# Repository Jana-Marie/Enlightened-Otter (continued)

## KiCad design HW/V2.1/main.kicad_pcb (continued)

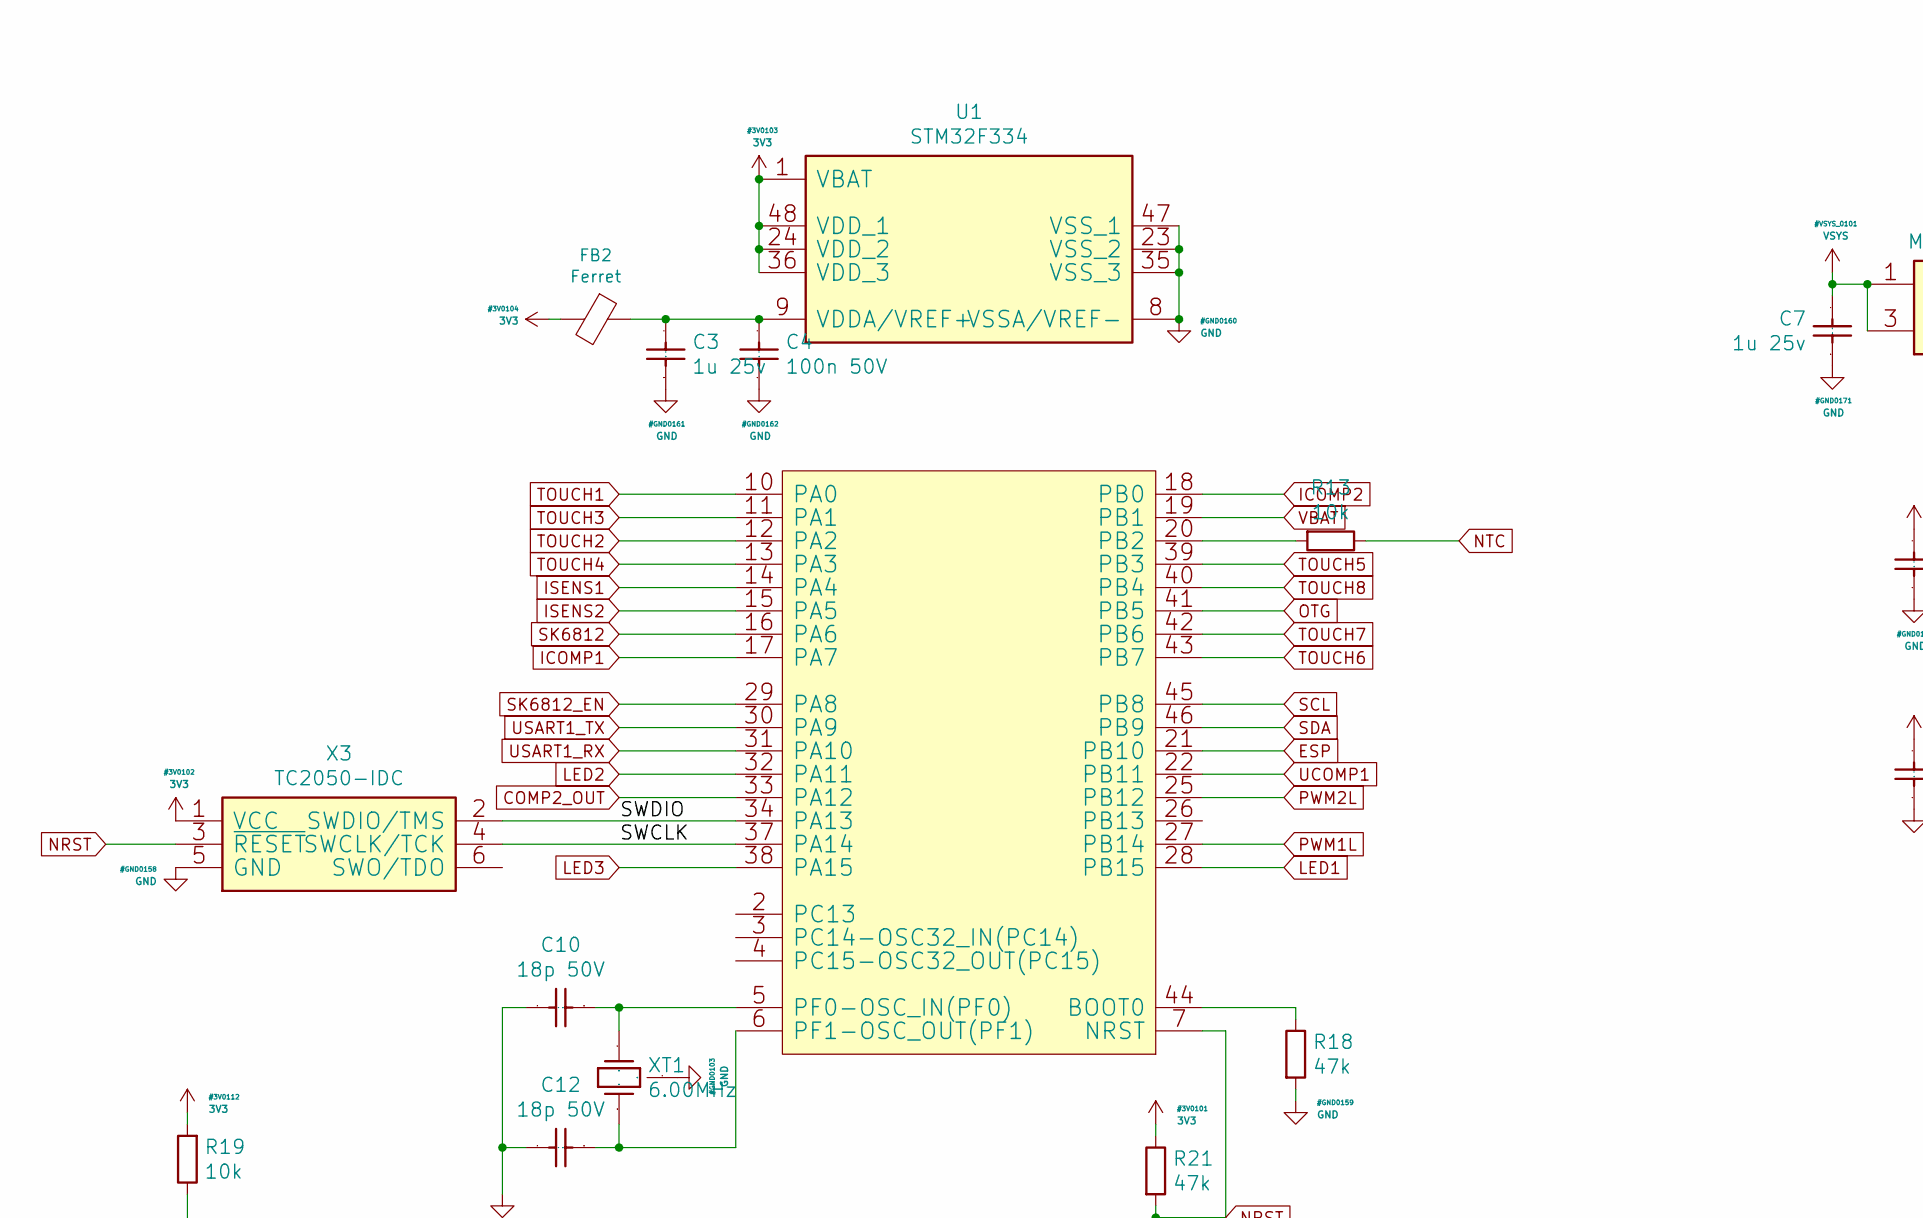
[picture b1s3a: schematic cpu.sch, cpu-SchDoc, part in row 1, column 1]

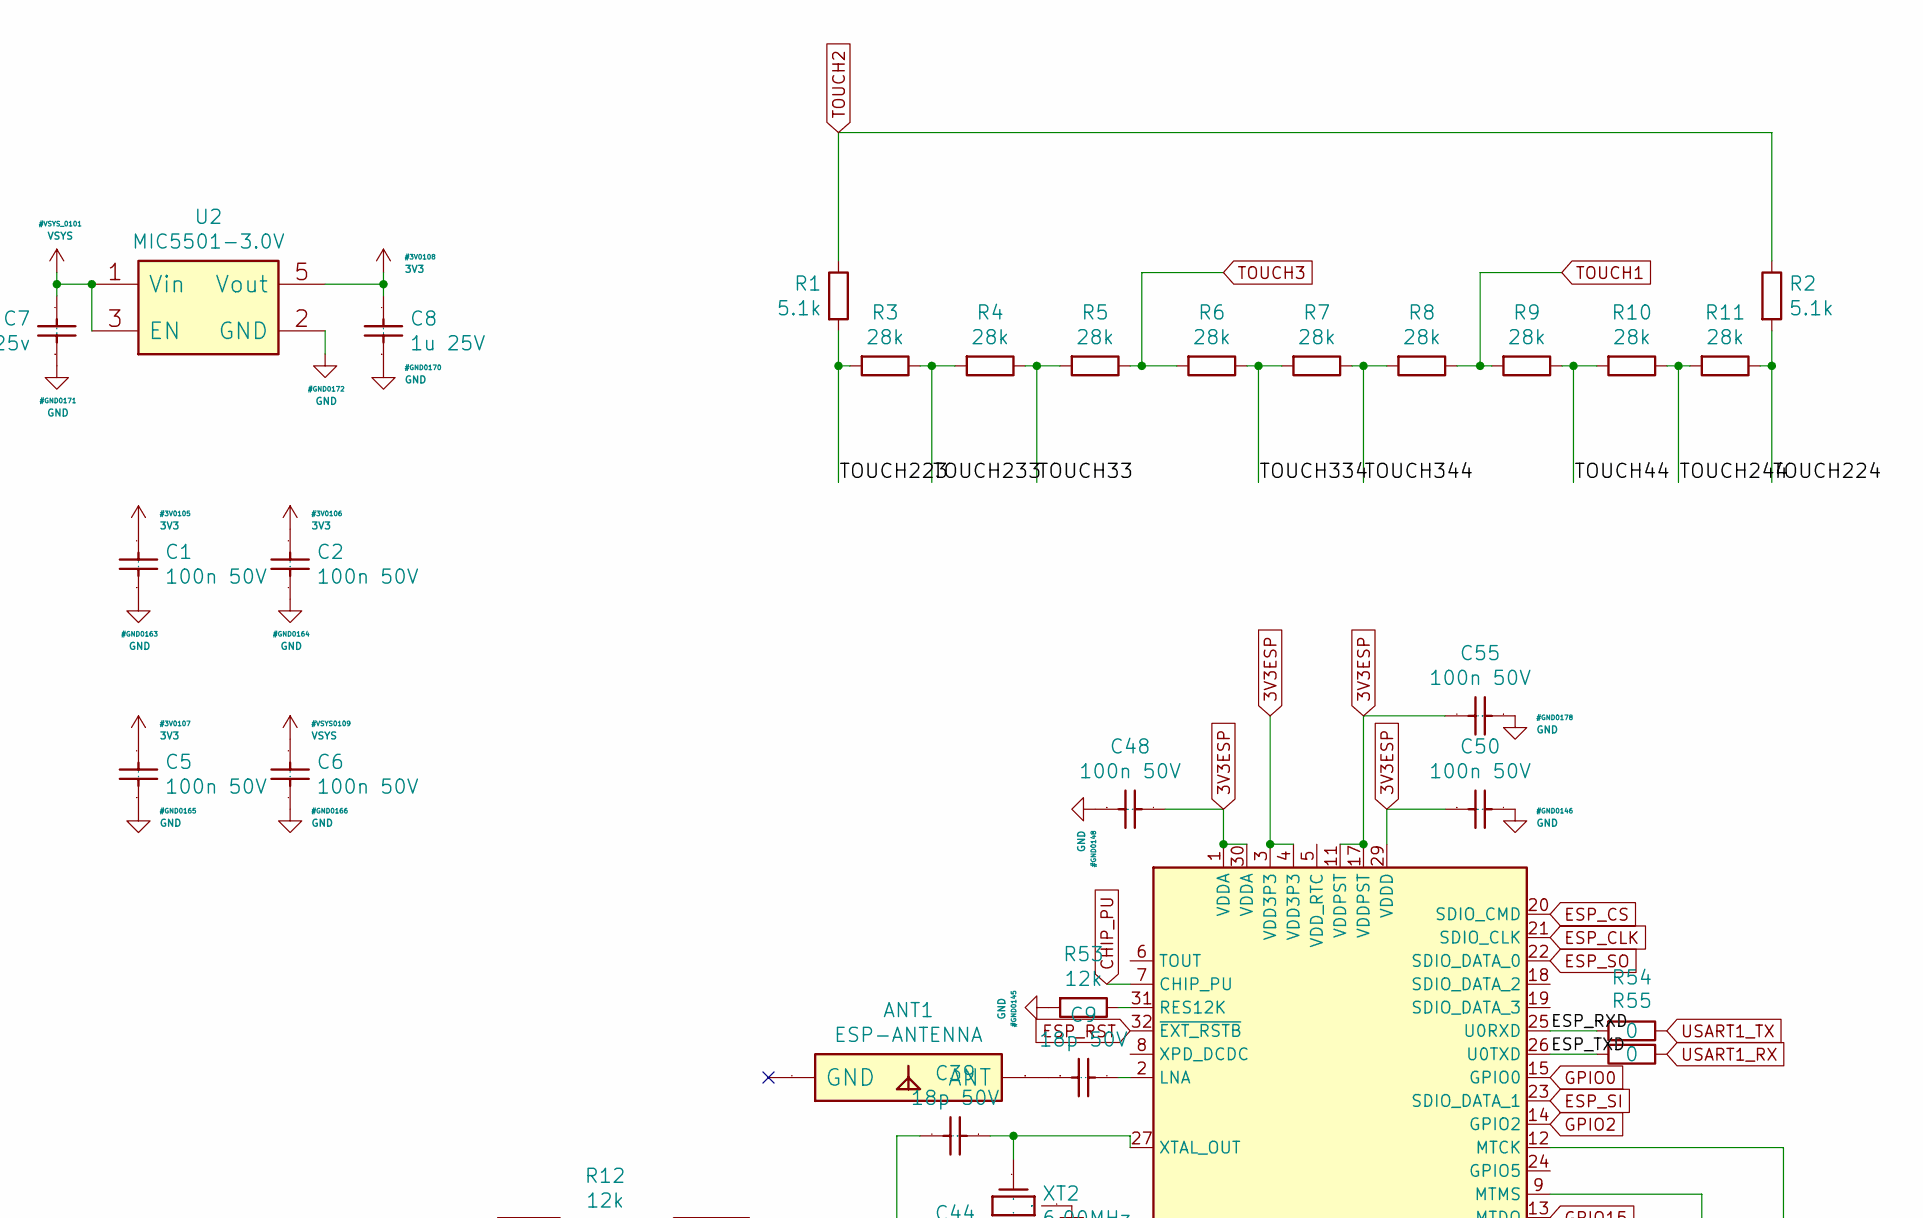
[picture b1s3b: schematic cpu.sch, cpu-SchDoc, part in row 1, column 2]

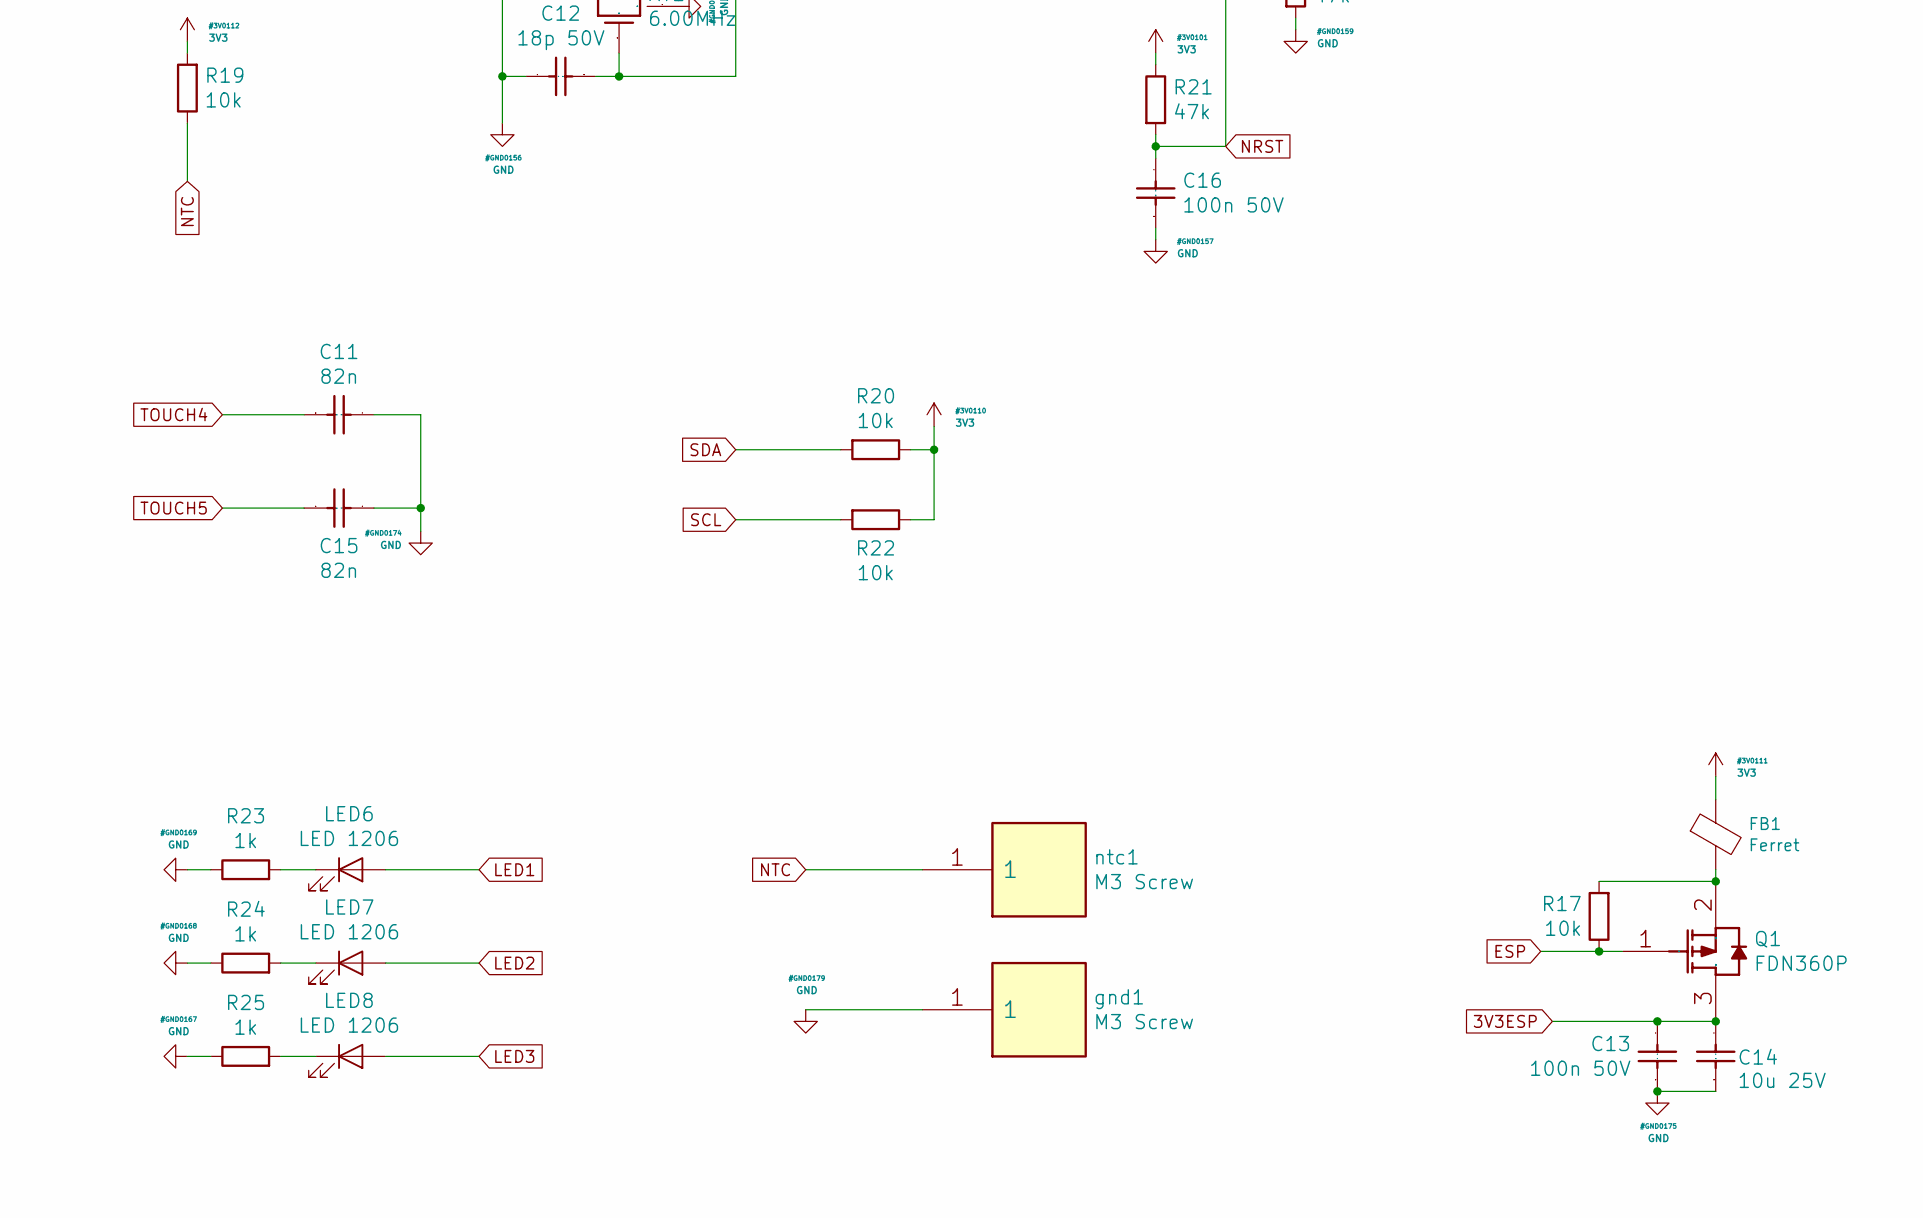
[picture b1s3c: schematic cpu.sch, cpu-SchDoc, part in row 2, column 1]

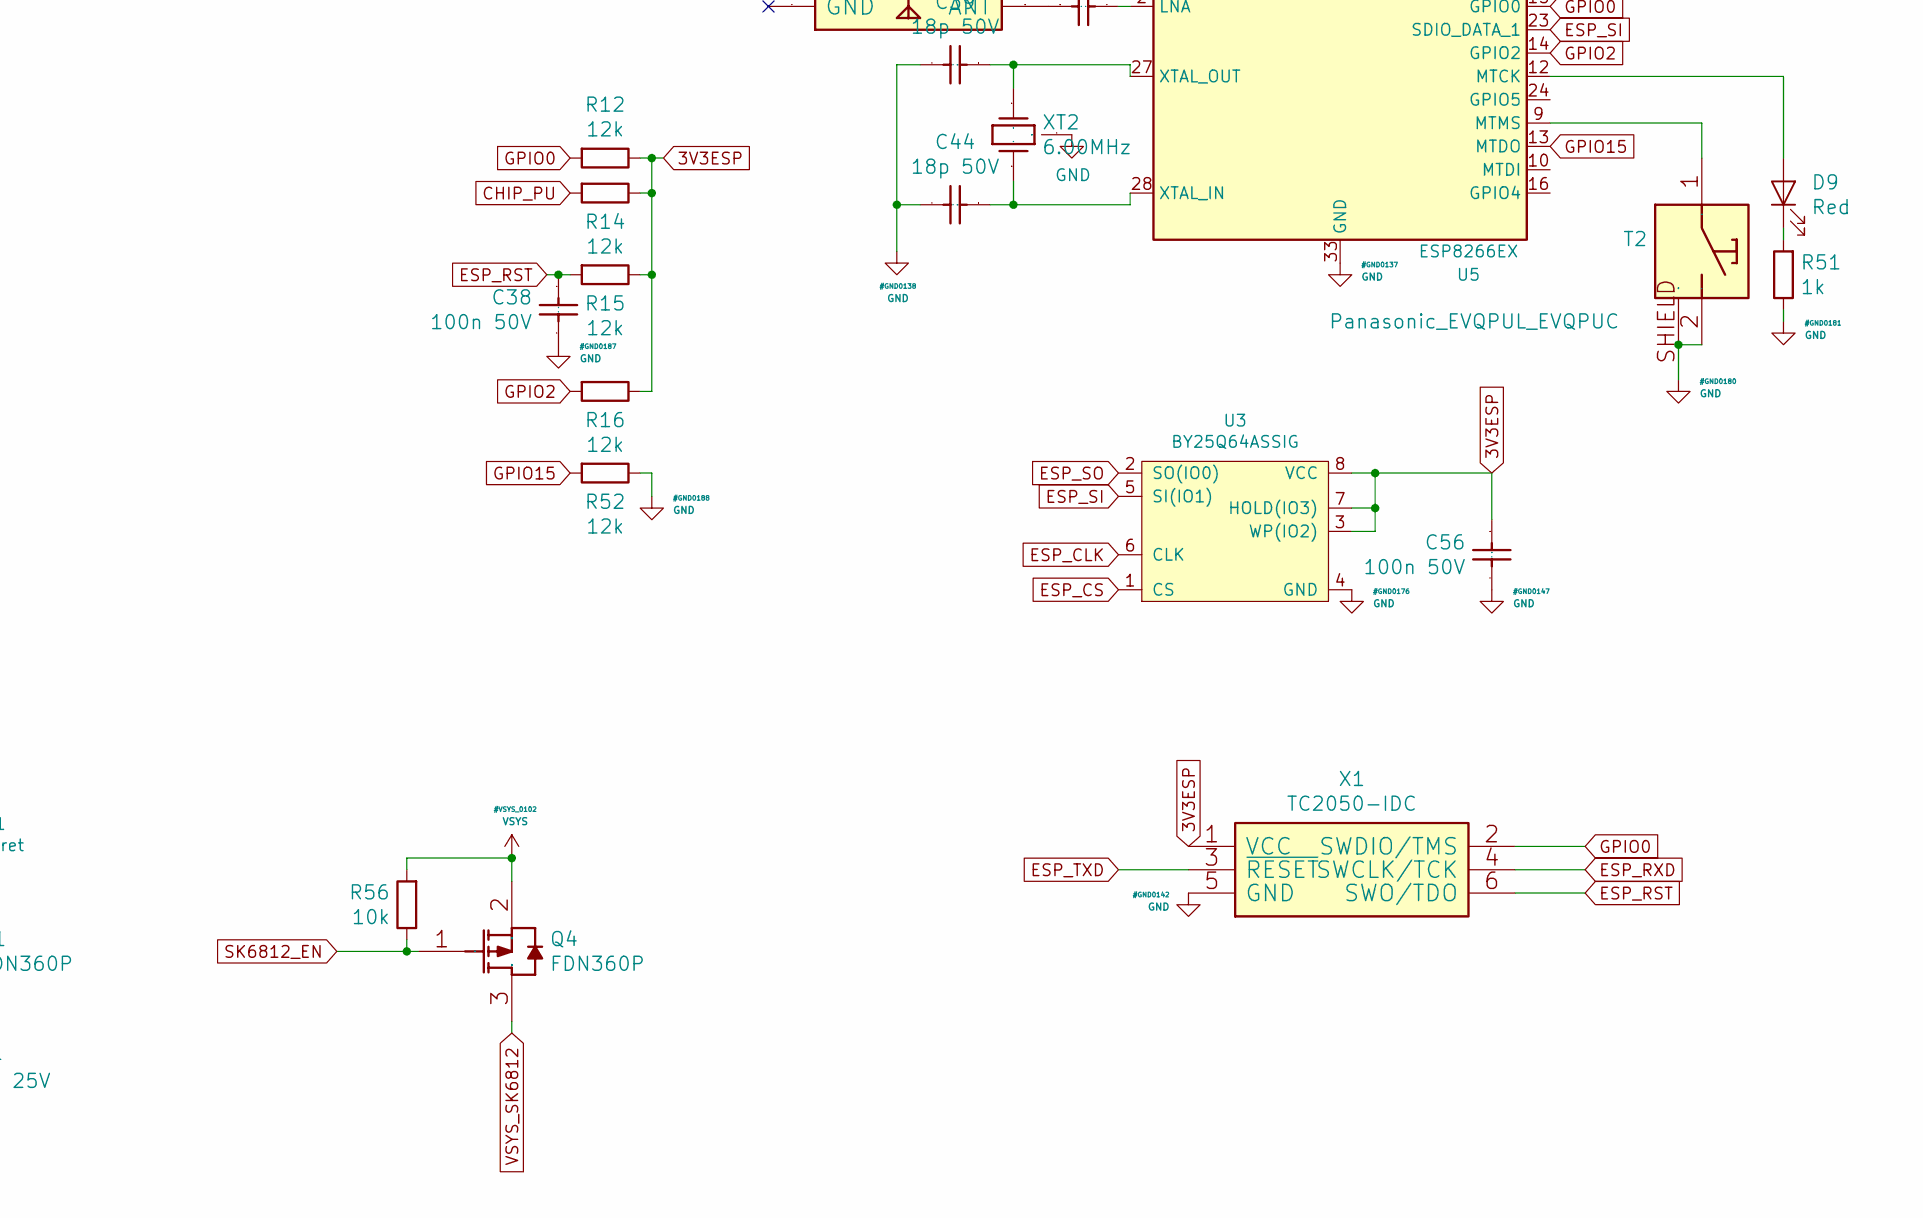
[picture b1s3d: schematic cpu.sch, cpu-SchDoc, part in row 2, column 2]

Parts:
ANT1: ESP-ANTENNA; AN9520_Rainsun
C1, C2, C4, C5, C6, C13, C16, C38, C48, C50, C55, C56: 100n 50V; C_0603_1608Metric
C3, C7: 1u 25v; C_0603_1608Metric
C8: 1u 25V; C_0603_1608Metric
C9, C10, C12, C39, C44: 18p 50V; C_0603_1608Metric
C11, C15: 82n; C_0603_1608Metric
C14: 10u 25V; C_0805_2012Metric
D9: Red; LED_0603_1608Metric
FB1, FB2: Ferret; L_0805_2012Metric
LED6, LED7, LED8: LED 1206; LED_1206_3216_BACK
Q1, Q4: FDN360P; SOT-23
R1, R2: 5.1k; R_0603_1608Metric
R3, R4, R5, R6, R7, R8, R9, R10, R11: 28k; R_0603_1608Metric
R12, R14, R15, R16, R52, R53: 12k; R_0603_1608Metric
R13, R17, R19, R20, R22, R56: 10k; R_0603_1608Metric
R18, R21: 47k; R_0603_1608Metric
R23, R24, R25, R51: 1k; R_0603_1608Metric
R54, R55: 0; R_0603_1608Metric
T2: Panasonic_EVQPUL_EVQPUC
U1: STM32F334; TQFP-48_7x7mm_P0.5mm
U2: MIC5501-3.0V; SOT-23-5
U3: BY25Q64ASSIG; SSOP-8_5.25x5.24mm_P1.27mm_WIDE_MULTI
U5: ESP8266EX; QFN-32-1EP_5x5mm_P0.5mm_EP3.45x3.45mm
X1, X3: TC2050-IDC; TC2030
XT1, XT2: 6.00MHz; Oscillator_3225
gnd1: M3 Screw; M3_Screw
ntc1: M3 Screw; M3_Screw

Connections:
3V3: C1.2, C2.2, C5.2, C8.2, FB1.1, FB2.2, R19.2, R20.1, R21.1, R22.1, U1.1 (VBAT), U1.24 (VDD_2), U1.36 (VDD_3), U1.48 (VDD_1), U2.5 (Vout), X3.1 (VCC); also elsewhere on the board
3V3ESP: C13.2, C14.2, C48.2, C50.1, C55.2, C56.1, Q1.3 (DRAIN), R12.1, R14.1, R15.1, R16.1, U3.3 (WP(IO2)), U3.7 (HOLD(IO3)), U3.8 (VCC), U5.1 (VDDA), U5.3 (VDD3P3), U5.4 (VDD3P3), U5.11 (VDDPST), U5.17 (VDDPST), U5.29 (VDDD), U5.30 (VDDA), X1.1 (VCC)
/cpu/SWCLK: U1.37 (PA14), X3.4 (SWCLK/TCK)
/cpu/SWDIO: U1.34 (PA13), X3.2 (SWDIO/TMS)
/cpu/TOUCH33: R4.1, R5.2
/cpu/TOUCH44: R9.1, R10.2
/cpu/TOUCH223: R1.2, R3.2
/cpu/TOUCH224: R2.2, R11.1
/cpu/TOUCH233: R3.1, R4.2
/cpu/TOUCH244: R10.1, R11.2
/cpu/TOUCH334: R6.1, R7.2
/cpu/TOUCH344: R7.1, R8.2
CHIP_PU: R14.2, U5.7 (CHIP_PU)
COMP2_OUT: U1.33 (PA12)
ESP: Q1.1 (GATE), R17.1, U1.21 (PB10)
ESP_CLK: U3.6 (CLK), U5.21 (SDIO_CLK)
ESP_CS: U3.1 (CS), U5.20 (SDIO_CMD)
ESP_RST: C38.1, R15.2, U5.32 (~EXT_RSTB~), X1.6 (SWO/TDO)
ESP_RXD: R54.2, U5.25 (U0RXD), X1.4 (SWCLK/TCK)
ESP_SI: U3.5 (SI(IO1)), U5.23 (SDIO_DATA_1)
ESP_SO: U3.2 (SO(IO0)), U5.22 (SDIO_DATA_0)
ESP_TXD: R55.2, U5.26 (U0TXD), X1.3 (~RESET)
GND: C1.1, C2.1, C3.1, C4.1, C5.1, C6.1, C7.1, C8.1, C10.2, C11.2, C12.2, C13.1, C14.1, C15.2, C16.1, C38.2, C39.2, C44.2, C48.1, C50.2, C55.1, C56.2, R18.2, R23.1, R24.1, R25.1, R51.1, R52.1, R53.2, T2.2, T2.SHIELD, U1.8 (VSSA/VREF-), U1.23 (VSS_2), U1.35 (VSS_3), U1.47 (VSS_1), U2.2 (GND), U3.4 (GND), U5.33 (GND), X1.5 (GND), X3.5 (GND), XT1.2 (OUT), XT1.4 (OUT), XT2.2 (OUT), XT2.4 (OUT), gnd1.1; also elsewhere on the board
GPIO0: R12.2, U5.15 (GPIO0), X1.2 (SWDIO/TMS)
GPIO2: R16.2, U5.14 (GPIO2)
GPIO15: R52.2, U5.13 (MTDO)
ICOMP1: U1.14 (PA4), U1.17 (PA7); also elsewhere on the board
ICOMP2: U1.15 (PA5), U1.18 (PB0); also elsewhere on the board
LED1: LED6.2 (A), U1.28 (PB15)
LED2: LED7.2 (A), U1.32 (PA11)
LED3: LED8.2 (A), U1.38 (PA15)
NRST: C16.2, R21.2, U1.7 (NRST), X3.3 (~RESET)
NTC: R13.1, R19.1, ntc1.1
unnamed: ANT1.1 (ANT), C9.1
unnamed: C3.2, C4.2, FB2.1, U1.9 (VDDA/VREF+)
unnamed: C9.2, U5.2 (LNA)
unnamed: C10.1, U1.5 (PF0-OSC_IN(PF0)), XT1.3 (IN)
unnamed: C12.1, U1.6 (PF1-OSC_OUT(PF1)), XT1.1 (IN)
unnamed: C39.1, U5.27 (XTAL_OUT), XT2.3 (IN)
unnamed: C44.1, U5.28 (XTAL_IN), XT2.1 (IN)
unnamed: D9.1 (K), R51.2
unnamed: D9.2 (A), U5.12 (MTCK)
unnamed 61: U1.42 (PB6); also elsewhere on the board
unnamed: FB1.2, Q1.2 (SOURCE), R17.2
unnamed: LED6.1 (K), R23.2
unnamed: LED7.1 (K), R24.2
unnamed: LED8.1 (K), R25.2
unnamed: R13.2, U1.20 (PB2)
unnamed: R18.1, U1.44 (BOOT0)
unnamed: R53.1, U5.31 (RES12K)
unnamed: T2.1, U5.9 (MTMS)
OTG: U1.41 (PB5); also elsewhere on the board
PWM1L: U1.27 (PB14); also elsewhere on the board
PWM2L: U1.25 (PB12); also elsewhere on the board
SCL: R22.2, U1.45 (PB8); also elsewhere on the board
SDA: R20.2, U1.46 (PB9); also elsewhere on the board
SK6812: U1.16 (PA6); also elsewhere on the board
SK6812_EN: Q4.1 (GATE), R56.1, U1.29 (PA8)
TOUCH1: R8.1, R9.2, U1.10 (PA0)
TOUCH2: R1.1, R2.1, U1.12 (PA2)
TOUCH3: R5.1, R6.2, U1.11 (PA1)
TOUCH4: C11.1, U1.13 (PA3)
TOUCH5: C15.1, U1.39 (PB3)
TOUCH6: U1.43 (PB7)
TOUCH8: U1.40 (PB4)
UCOMP1: U1.22 (PB11); also elsewhere on the board
USART1_RX: R55.1, U1.31 (PA10)
USART1_TX: R54.1, U1.30 (PA9)
VBAT: U1.19 (PB1); also elsewhere on the board
VSYS: C6.2, C7.2, Q4.2 (SOURCE), R56.2, U2.1 (Vin), U2.3 (EN); also elsewhere on the board
VSYS_SK6812: Q4.3 (DRAIN); also elsewhere on the board

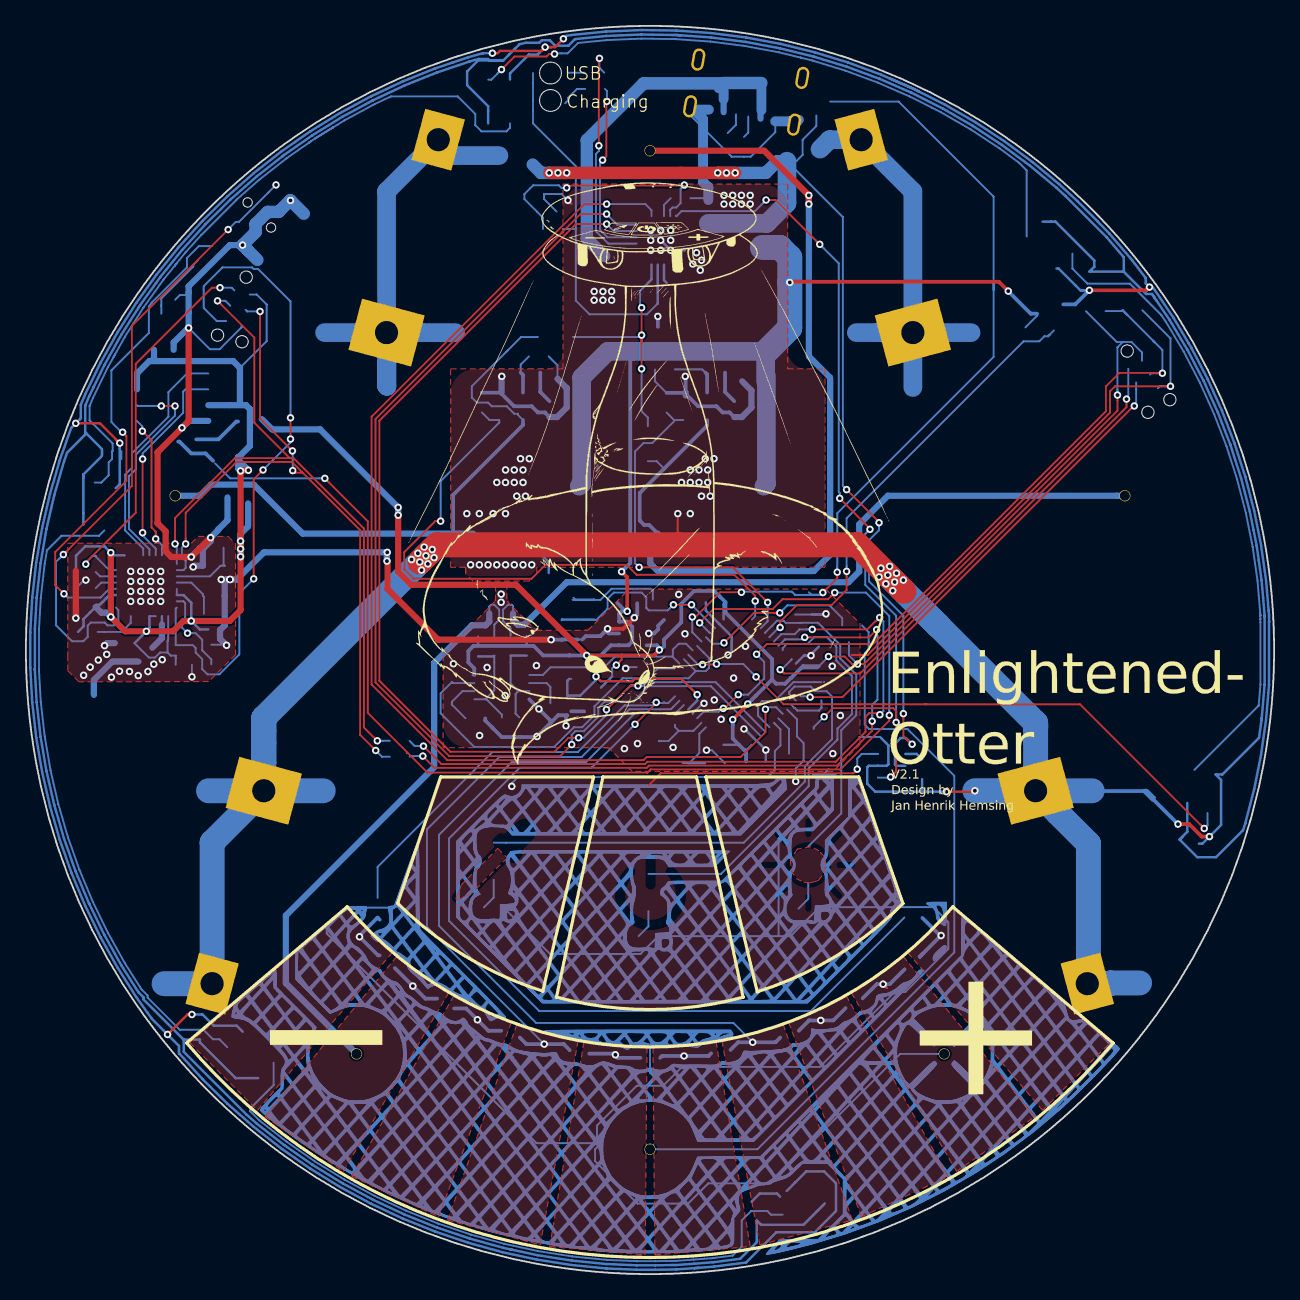
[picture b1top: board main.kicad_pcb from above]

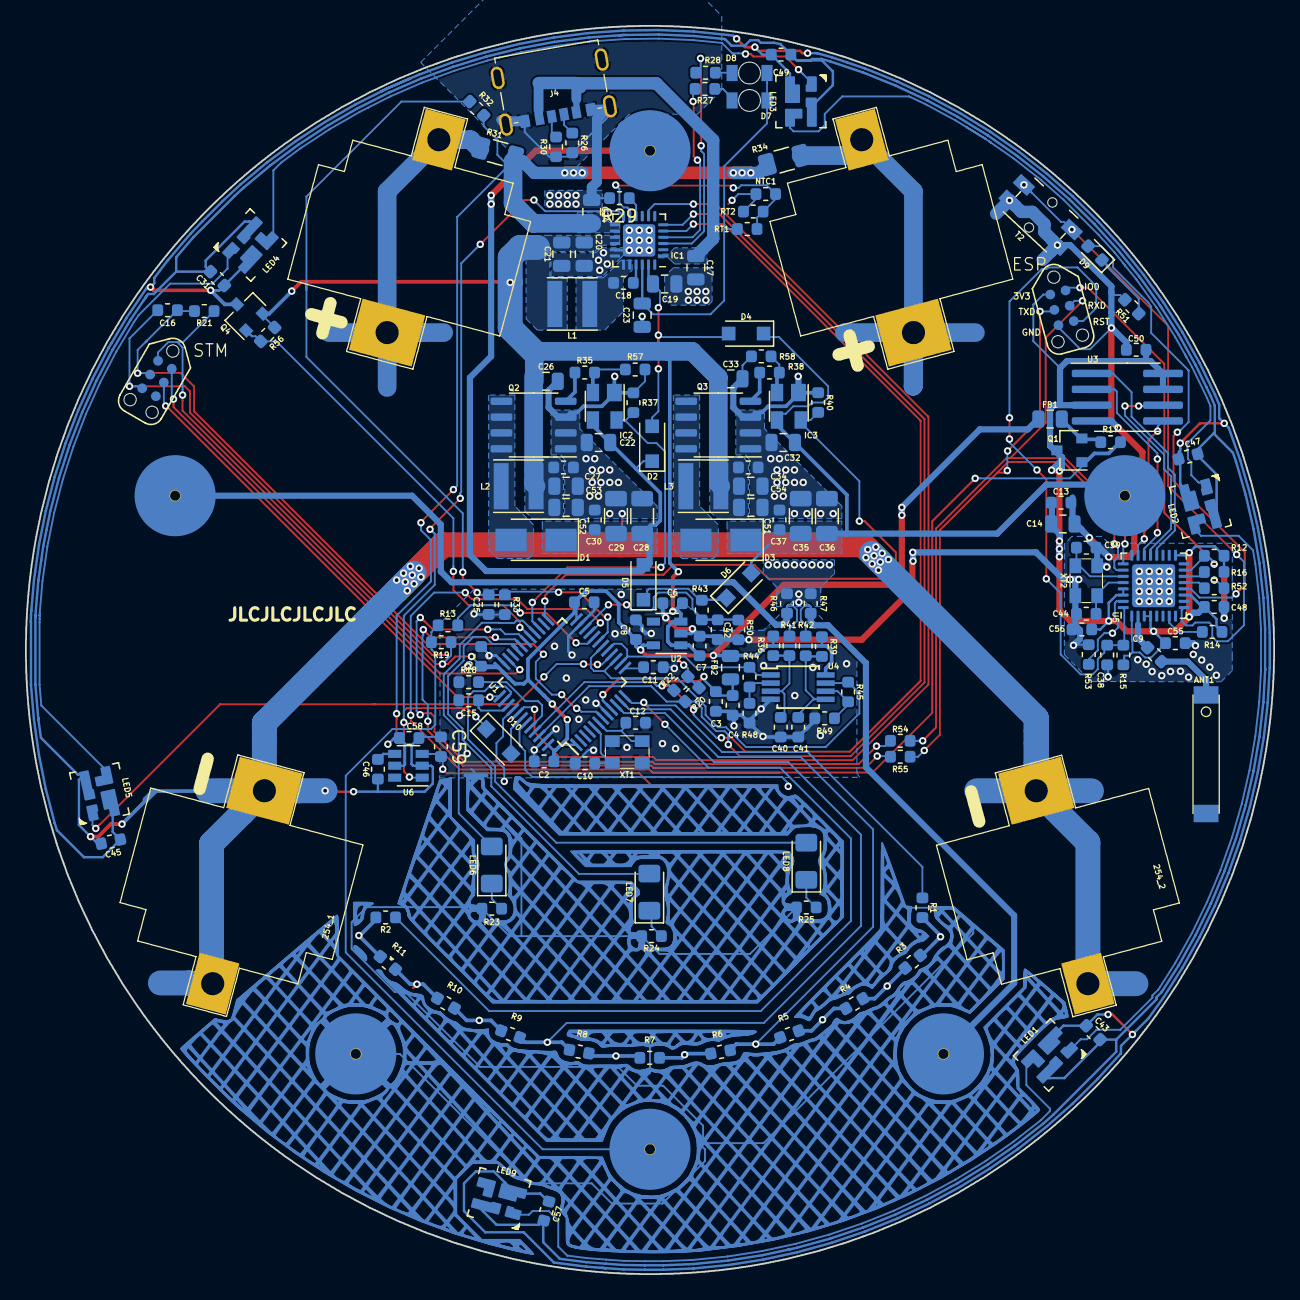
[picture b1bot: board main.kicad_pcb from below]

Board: 2 copper layers, 100.0 x 100.0 mm, 174 parts (173 on the bottom side), 108 nets.

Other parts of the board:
C46: DNP; C_0603_1608Metric
C58: 100n 50V; C_0603_1608Metric
C59: 18p 50V; C_0603_1608Metric
D10: D; D_SOD-123F
G1: LOGO; power_0707
U6: BS801B; SOT-23-6

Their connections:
GND: C46.1, C58.2, C59.1, U6.2; also elsewhere on the board
unnamed: C46.2, U6.4
unnamed 61: D10.2; also elsewhere on the board
TOUCH7: C59.2, U6.3
TOUCH_POWER: D10.1, U6.1; also elsewhere on the board
VBAT+: C58.1, U6.5; also elsewhere on the board

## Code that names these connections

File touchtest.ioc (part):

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Mcu.Name=STM32F334C(4-6-8)Tx
Mcu.Package=LQFP48
Mcu.UserName=STM32F334C6Tx
PA0.Mode=G1_IO1-Sampling
PA0.Signal=TSC_G1_IO1
PA1.Mode=G1_IO2-Channel
PA1.Signal=TSC_G1_IO2
PA10.Mode=Asynchronous
PA10.Signal=USART1_RX
PA11.GPIOParameters=GPIO_Label
PA11.GPIO_Label=LED2
PA11.Signal=GPIO_Output
PA12.Mode=ExternalOutput
PA12.Signal=COMP2_OUT
PA13.Mode=Serial_Wire
PA13.Signal=SYS_JTMS-SWDIO
PA14.Mode=Serial_Wire
PA14.Signal=SYS_JTCK-SWCLK
PA15.GPIOParameters=GPIO_Label
PA15.GPIO_Label=LED3
PA15.Signal=GPIO_Output
PA2.Mode=G1_IO3-Channel
PA2.Signal=TSC_G1_IO3
PA3.Mode=G1_IO4-Channel
PA3.Signal=TSC_G1_IO4
PA4.Mode=IN1-Single-Ended
PA4.Signal=ADC2_IN1
PA5.Mode=IN2-Single-Ended
PA5.Signal=ADC2_IN2
PA6.Mode=IN3-Single-Ended
PA6.Signal=ADC2_IN3
PA7.Mode=INP
PA7.Signal=COMP2_INP
PA8.GPIOParameters=GPIO_Label
PA8.GPIO_Label=LED1
PA8.Signal=GPIO_Output
PA9.Mode=Asynchronous
PA9.Signal=USART1_TX
PB0.Mode=INP
PB0.Signal=COMP4_INP
PB1.Mode=IN12-Single-Ended
PB1.Signal=ADC1_IN12
PB11.Mode=INP
PB11.Signal=COMP6_INP
PB12.Mode=Output_TC1TC2
PB12.Signal=HRTIM1_CHC1
PB13.Mode=Output_TC1TC2
PB13.Signal=HRTIM1_CHC2
PB14.Mode=Output_TD1TD2
PB14.Signal=HRTIM1_CHD1
PB15.Mode=Output_TD1TD2
PB15.Signal=HRTIM1_CHD2
PB2.Mode=IN12-Single-Ended
PB2.Signal=ADC2_IN12
PB3.Mode=G5_IO1-Sampling
PB3.Signal=TSC_G5_IO1
PB4.Mode=G5_IO2-Channel
PB4.Signal=TSC_G5_IO2
PB6.Mode=G5_IO3-Channel
PB6.Signal=TSC_G5_IO3
PB7.Mode=G5_IO4-Channel
PB7.Signal=TSC_G5_IO4
PB8.Mode=I2C
PB8.Signal=I2C1_SCL
PB9.Mode=I2C
PB9.Signal=I2C1_SDA
PF0\ /\ OSC_IN.Mode=HSE-External-Oscillator
PF0\ /\ OSC_IN.Signal=RCC_OSC_IN
PF1\ /\ OSC_OUT.Mode=HSE-External-Oscillator
PF1\ /\ OSC_OUT.Signal=RCC_OSC_OUT
RCC.HSEPLLFreq_Value=8000000
RCC.HSE_VALUE=8000000
RCC.SYSCLKFreq_VALUE=72000000
RCC.SYSCLKSourceVirtual=RCC_SYSCLKSOURCE_PLLCLK
board=touchtest

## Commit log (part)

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2018-08-17 changed regulator cycle time to 63
2018-08-18 update gitignore
2018-08-18 changed parameters
2018-08-19 added power button state maschine
2018-08-19 fixed led state
2018-08-19 fixed indent
2018-08-19 fixed variable names
2018-08-19 commented code
2018-08-19 added stop condition on turn off
2018-08-19 fixed linewrap
2018-08-19 renamed Variables
2018-08-19 added LED turnoff during off state
2018-08-19 fixed comment indents
2018-08-19 added dim power led during turn off
2018-08-19 added TIM2 CH1 for pwm for the power led
2018-08-19 made led turnoff brightness settings global
2018-08-19 moved averaging filter coeffizient
2018-08-20 moved static variables to defines
2018-08-20 added FILT makro
2018-08-20 fixed typo
2018-08-20 added set_brightness functiom
2018-08-20 moved inti functions to seperate file
2018-08-20 added license
2018-08-20 optimized variables
2018-08-20 changed inductors, current can now go up to 400mA
2018-08-20 renamed define
2018-08-20 added basic gamma correction
2018-08-20 changed print ruotine
2018-08-20 changed filter values
2018-08-21 update schematic
2018-08-21 added gamma table generator
2018-08-21 fixed script
2018-08-21 added better gamma calculation
2018-08-21 added gamma table
2018-08-21 changed variables, fixed output
2018-08-21 remved ADC1 as it is not needed anymore
2018-08-21 fixed slider "jumps"
2018-08-21 added TSC interrupt
2018-08-21 TSC works now in interrupt mode, slider is off by 1 pad
2018-08-21 fixed off by one bug
2018-08-21 fixed TSC bug, Gate resistors had to be increased
2018-08-22 cleanup and added defines
2018-08-22 cleanup and moved static variables to defines
2018-08-22 Update Todos in readme
2018-08-22 FLT1 works now, was a logic error
2018-08-22 FLT2 works now too, WW flt
2018-08-22 Overvoltage FLT works now too
2018-08-22 fixed init
2018-08-22 fixed recurrent FLT
2018-08-22 added gamma correction
2018-08-22 fixed warning
2018-08-22 gamma correction is now working
2018-08-22 improved filter values
2018-08-22 added LED temperature measurement
2018-08-23 removed ADC1 config changed comment style
2018-08-23 moved global variables into structs
2018-08-23 fixed struct init
2018-08-23 reformat UI task
2018-08-23 added variable to struct
2018-08-23 fixed error
2018-08-23 removed code
2018-08-23 added UI struct
2018-08-23 added LED_task
2018-08-23 renamed variable
2018-08-23 reformated code
2018-08-23 moved functions to ultils.c
2018-08-23 fixed power failure error
2018-08-23 fixed gamma bug
2018-08-23 added ntc calculation
2018-08-24 chanegd parameters
2018-08-24 added Hardware V1.1 Schematic
2018-08-24 added Gerber files
2018-08-24 fixed missing part
2018-08-24 added fixture
2018-08-25 testing
2018-08-25 testing, messy, needs to be sorted
2018-08-25 additional files
2018-08-25 added 3D printable inlet
2018-08-25 added Inlet
2018-08-26 added images
2018-08-26 chnaged parameters
2018-08-26 added basic shipping mode
2018-08-27 reformat turn off/on task
2018-08-27 created status struct
2018-08-27 added make flash_st
2018-08-27 reformat code
2018-08-28 reverted gamma correction for testing
2018-09-07 added input averaging
2018-09-08 reduced button threshold
2018-09-08 fixed slow turnoff
2018-09-08 added battery voltage display
2018-09-11 update gamma table
2018-09-11 added improved gamma function
2018-09-11 reformat variables
2018-09-11 added advanced gamma correction
2018-09-11 removed buggy battery voltage display, added gamma correction
2018-09-11 added specs
2018-09-12 updated settings
2018-09-17 fixed touch slider scale
2018-09-17 added better touch sensing
2018-09-17 changed TSC init
2018-09-17 removed touch input averaging (not needed anymore)
2018-09-18 created new gamma table
2018-09-18 added flickerfree gamma
2018-09-18 changed variables
2018-09-18 added more gamma values
2018-09-18 moved adc sampling time
2018-09-21 added interpolation for gamma
2018-09-29 added I2C dma mode
2018-09-29 fixed i2c receive bug
2018-09-29 added state maschine to measure all RT parameters
2018-09-29 important readme update
2018-09-30 kind of shitty fixed i2c
2018-09-30 added more RT registers
2018-09-30 i2c is now not blocking and failed i2c does not cause a crash anymore
2018-09-30 has now low battery turnoff
2018-09-30 fixed i2c
2018-12-19 added V2 moved V1.1 dokumentation
2018-12-20 updated to HW2.0
2018-12-20 moved files
2019-01-16 fixed touch for V2
2019-01-17 changed stuff, works now with V2
2019-01-18 added comments
2019-01-18 removed empty variable
2019-01-18 fixed LED names
2019-01-18 added UI init
2019-01-18 moved 3D files
2019-02-09 updated stuff
2019-04-13 fixed pwm
2019-08-04 added Hardware V2.1, complete redesign in KiCAD
2019-08-04 added schematic pdf
2019-09-06 updated firmware to Hardware V2.1, fixed controller
2019-09-06 fixed ADC
2019-09-06 fixed TSC slider
2019-09-06 tested RT
2019-09-06 updated values
2019-09-06 RT9466 ADC does not work properly, shutdown works now
2019-09-06 UVP added
2019-09-06 added pwm on led2
2019-09-06 fixed opamp
2019-09-07 added sk6812 functionality
2019-09-08 added led functions, fixed current gain, added flt
2019-09-08 fixed voltage divider for current measurement
2019-09-08 added touch ic, fixed sk6812
2019-09-08 routed board
2019-09-08 enlarged pads
2019-09-08 drc done
2019-09-08 exported gerber
2019-09-08 finished animations, battery indicator still missing, fixed hardware bugs
2019-09-08 added images of v2.1
2019-09-08 fixed two bugs
2019-09-08 renamed images
2019-09-08 updated makefile
2019-09-08 removed old images
2019-09-09 updated images
2019-11-24 added LED PCB
2020-01-01 updated bom
2020-01-03 updated fw
2020-01-05 fixed values
2020-03-21 increased timer resolution by 32
2020-03-23 fixed touch bugs
2020-03-23 fixed touch
2020-03-24 fixed mobile touch bug
2020-03-29 enchanced touch
2020-03-30 added hardfault handling, double tap for maximum brightness
2020-03-30 added fault inputs
